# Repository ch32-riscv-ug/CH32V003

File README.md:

# CH32V003

<!-- This file is generated from ch32-riscv-ug/ch32-device-data (index/ + evidence/ + pipeline/build/build_readme.py). Edit there, not here. -->

[Choose a part](#product-comparison) &middot; [Documents](#documents) &middot; [Pin maps](#pin-maps--alternate-functions) &middot; [Pin viewer](https://ch32-riscv-ug.github.io/ch32-device-data/pins.html?chip=CH32V003) &middot; [Errata](#errata) &middot; [Examples](#evt-examples) &middot; [Address map](#address-map)

## Quick start

Programming and debug: **1-wire SDI** (WCH-Link, `Serial Debug Interface`).

### Debug / serial defaults

Where these land **without writing a remap register**. SWD is live at reset; the UART pads are not -- the pin must still be put into alternate-function mode. See `route` in evidence/README.ja.md.

| Series | SWDIO | SWCLK | UART TX | UART RX |
|---|---|---|---|---|
| CH32V003 | PD1 | - | PD5 (USART1) | PD6 (USART1) |

### Datasheets and reference manual

- CH32V003DS0.PDF (datasheet): [English](https://ch32-riscv-ug.github.io/CH32V003/datasheet_en/CH32V003DS0.PDF) · [中文](https://ch32-riscv-ug.github.io/CH32V003/datasheet_zh/CH32V003DS0.PDF)
- CH32V003RM.PDF (reference manual): [English](https://ch32-riscv-ug.github.io/CH32V003/datasheet_en/CH32V003RM.PDF) · [中文](https://ch32-riscv-ug.github.io/CH32V003/datasheet_zh/CH32V003RM.PDF)

## Series

| Series | Core | ISA | Flash | SRAM | Main clock | VDD | Packages | Products | Official |
|---|---|---|---|---|---|---|---|---|---|
| **CH32V003** | QingKe V2A | RV32EC | 16K | 2K | 48 MHz | 2.7-5.5V | QFN20,SOP16,SOP8,TSSOP20 | 4 | [en](https://www.wch-ic.com/products/CH32V003.html) / [zh](https://www.wch.cn/products/CH32V003.html) |

## Product comparison

### CH32V003 product comparison

Only the 3 rows that differ between these 4 products; the other 9 are the same for all of them.

| | [CH32V003&#8203;A4M6](https://ch32-riscv-ug.github.io/ch32-device-data/pins.html?chip=CH32V003A4M6)&#8203;(SOP16) | [CH32V003&#8203;F4P6](https://ch32-riscv-ug.github.io/ch32-device-data/pins.html?chip=CH32V003F4P6)&#8203;(TSSOP20) | [CH32V003&#8203;F4U6](https://ch32-riscv-ug.github.io/ch32-device-data/pins.html?chip=CH32V003F4U6)&#8203;(QFN20) | [CH32V003&#8203;J4M6](https://ch32-riscv-ug.github.io/ch32-device-data/pins.html?chip=CH32V003J4M6)&#8203;(SOP8) |
|---|---|---|---|---|
| **GPIO** | 14 | 18 | 18 | 6 |
| ADC Channel No. | 6 | 8 | 8 | 6 |
| SPI | - | 1 | 1 | - |

<details><summary>All 12 rows</summary>

| | [CH32V003&#8203;A4M6](https://ch32-riscv-ug.github.io/ch32-device-data/pins.html?chip=CH32V003A4M6)&#8203;(SOP16) | [CH32V003&#8203;F4P6](https://ch32-riscv-ug.github.io/ch32-device-data/pins.html?chip=CH32V003F4P6)&#8203;(TSSOP20) | [CH32V003&#8203;F4U6](https://ch32-riscv-ug.github.io/ch32-device-data/pins.html?chip=CH32V003F4U6)&#8203;(QFN20) | [CH32V003&#8203;J4M6](https://ch32-riscv-ug.github.io/ch32-device-data/pins.html?chip=CH32V003J4M6)&#8203;(SOP8) |
|---|---|---|---|---|
| **Flash** | 16K | 16K | 16K | 16K |
| **SRAM** | 2K | 2K | 2K | 2K |
| **GPIO** | 14 | 18 | 18 | 6 |
| **Temperature** | -40..85C | -40..85C | -40..85C | -40..85C |
| Advanced-control timer | 1 | 1 | 1 | 1 |
| General-purpose timer | 1 | 1 | 1 | 1 |
| Watchdog | 2 | 2 | 2 | 2 |
| System clock source | 3 | 3 | 3 | 3 |
| ADC Channel No. | 6 | 8 | 8 | 6 |
| I2C | 1 | 1 | 1 | 1 |
| SPI | - | 1 | 1 | - |
| USART | 1 | 1 | 1 | 1 |

</details>

## Block diagrams

### CH32V003

System block diagram from the [WCH product page](https://www.wch-ic.com/products/CH32V003.html).

<details><summary>Internal block diagram (datasheet)</summary>

</details>

## Documents

| Document | Kind | English | 中文 |
|---|---|---|---|
| CH32V003DS0.PDF | datasheet | [page](https://www.wch-ic.com/downloads/CH32V003DS0_PDF.html) [mirror](https://ch32-riscv-ug.github.io/CH32V003/datasheet_en/CH32V003DS0.PDF) v1.8 | [page](https://www.wch.cn/downloads/CH32V003DS0_PDF.html) [mirror](https://ch32-riscv-ug.github.io/CH32V003/datasheet_zh/CH32V003DS0.PDF) v1.8 |
| CH32V003RM.PDF | reference-manual | [page](https://www.wch-ic.com/downloads/CH32V003RM_PDF.html) [mirror](https://ch32-riscv-ug.github.io/CH32V003/datasheet_en/CH32V003RM.PDF) v1.9 | [page](https://www.wch.cn/downloads/CH32V003RM_PDF.html) [mirror](https://ch32-riscv-ug.github.io/CH32V003/datasheet_zh/CH32V003RM.PDF) v1.9 |
| CH32V003EVT.ZIP | evt | - | [page](https://www.wch.cn/downloads/CH32V003EVT_ZIP.html) [mirror](https://github.com/ch32-riscv-ug/CH32V003/tree/main/EVT) v2.2 |

### Evaluation boards

- board-manual:en: [CH32V00x Evaluation Board Reference-EN.pdf](https://ch32-riscv-ug.github.io/CH32V003/EVT/PUB/CH32V00x%20Evaluation%20Board%20Reference-EN.pdf)
- board-manual:zh: [CH32V00x评估板说明书.pdf](https://ch32-riscv-ug.github.io/CH32V003/EVT/PUB/CH32V00x%E8%AF%84%E4%BC%B0%E6%9D%BF%E8%AF%B4%E6%98%8E%E4%B9%A6.pdf)
- schematic-pdf: [CH32V00xSCH.pdf](https://ch32-riscv-ug.github.io/CH32V003/EVT/PUB/CH32V00xSCH.pdf)

1 board schematics under `EVT/PUB/SCHPCB/`: `CH32V003F4P6-R0`

## Packages & pinout drawings

Pinout drawings are in the datasheet (chapter *Pinouts*); each link opens at the page that carries the drawing:

| Package | Products | Datasheet | Outline |
|---|---|---|---|
| SOP16 | CH32V003A4M6 | [en](https://ch32-riscv-ug.github.io/CH32V003/datasheet_en/CH32V003DS0.PDF#page=12) / [zh](https://ch32-riscv-ug.github.io/CH32V003/datasheet_zh/CH32V003DS0.PDF#page=9) | [drawing](https://raw.githubusercontent.com/ch32-riscv-ug/WCH-common/main/image/package_SOP16.png) |
| TSSOP20 | CH32V003F4P6 | [en](https://ch32-riscv-ug.github.io/CH32V003/datasheet_en/CH32V003DS0.PDF#page=12) / [zh](https://ch32-riscv-ug.github.io/CH32V003/datasheet_zh/CH32V003DS0.PDF#page=9) | [drawing](https://raw.githubusercontent.com/ch32-riscv-ug/WCH-common/main/image/package_TSSOP20.png) |
| QFN20 | CH32V003F4U6 | [en](https://ch32-riscv-ug.github.io/CH32V003/datasheet_en/CH32V003DS0.PDF#page=12) / [zh](https://ch32-riscv-ug.github.io/CH32V003/datasheet_zh/CH32V003DS0.PDF#page=9) | [drawing](https://raw.githubusercontent.com/ch32-riscv-ug/WCH-common/main/image/package_QFN20.png) |
| SOP8 | CH32V003J4M6 | [en](https://ch32-riscv-ug.github.io/CH32V003/datasheet_en/CH32V003DS0.PDF#page=13) / [zh](https://ch32-riscv-ug.github.io/CH32V003/datasheet_zh/CH32V003DS0.PDF#page=9) | [drawing](https://raw.githubusercontent.com/ch32-riscv-ug/WCH-common/main/image/package_SOP8.png) |

## Pin maps & alternate functions

> [!NOTE]
> These are the **pin-table superset**: the datasheet prints one pad table for every product that shares a pinout, so a pad row does not mean this part has the peripheral. Use the product comparison table above for what a given part number contains.

### CH32V003 pin map

Pin functions (filterable): [ALL](https://ch32-riscv-ug.github.io/ch32-device-data/pins.html?chip=CH32V003) [ADC](https://ch32-riscv-ug.github.io/ch32-device-data/pins.html?chip=CH32V003&features=ADC) [I2C](https://ch32-riscv-ug.github.io/ch32-device-data/pins.html?chip=CH32V003&features=I2C) [SPI](https://ch32-riscv-ug.github.io/ch32-device-data/pins.html?chip=CH32V003&features=SPI) [SYS](https://ch32-riscv-ug.github.io/ch32-device-data/pins.html?chip=CH32V003&features=SYS) [TIM](https://ch32-riscv-ug.github.io/ch32-device-data/pins.html?chip=CH32V003&features=TIM) [UART](https://ch32-riscv-ug.github.io/ch32-device-data/pins.html?chip=CH32V003&features=UART) [USB](https://ch32-riscv-ug.github.io/ch32-device-data/pins.html?chip=CH32V003&features=USB)

| Pin name | Type | [CH32V003&#8203;A4M6](https://ch32-riscv-ug.github.io/ch32-device-data/pins.html?chip=CH32V003A4M6)&#8203;(SOP16) | [CH32V003&#8203;F4P6](https://ch32-riscv-ug.github.io/ch32-device-data/pins.html?chip=CH32V003F4P6)&#8203;(TSSOP20) | [CH32V003&#8203;F4U6](https://ch32-riscv-ug.github.io/ch32-device-data/pins.html?chip=CH32V003F4U6)&#8203;(QFN20) | [CH32V003&#8203;J4M6](https://ch32-riscv-ug.github.io/ch32-device-data/pins.html?chip=CH32V003J4M6)&#8203;(SOP8) | Notes |
|---|---|---|---|---|---|---|
| PA1 | I/O/A | 12 | 5 | 2 | 1 | OSC |
| PA2 | I/O/A | 13 | 6 | 3 | 3 | OSC |
| PC0 | I/O | 16 | 10 | 7 | - |  |
| PC1 | I/O/FT | 1 | 11 | 8 | 5 |  |
| PC2 | I/O/FT | 2 | 12 | 9 | 6 |  |
| PC3 | I/O | 3 | 13 | 10 | - |  |
| PC4 | I/O/A | 4 | 14 | 11 | 7 |  |
| PC5 | I/O/FT | - | 15 | 12 | - |  |
| PC6 | I/O/FT | 5 | 16 | 13 | - |  |
| PC7 | I/O | 6 | 17 | 14 | - |  |
| PD0 | I/O/A | - | 8 | 5 | - |  |
| PD1 | I/O/A | 7 | 18 | 15 | 8 | SWDIO |
| PD2 | I/O/A | - | 19 | 16 | - |  |
| PD3 | I/O/A | - | 20 | 17 | - |  |
| PD4 | I/O/A | 8 | 1 | 18 | 8 |  |
| PD5 | I/O/A | 9 | 2 | 19 | 8 | UART TX (USART1) |
| PD6 | I/O/A | 10 | 3 | 20 | 1 | UART RX (USART1) |
| PD7 | I/O/A | 11 | 4 | 1 | - |  |
| VDD | P | 15 | 9 | 6 | 4 |  |
| VSS | P | 14 | 7 | 4/EP | 2 |  |

<details><summary><b>CH32V003 alternate functions</b></summary>

| Pad | default | (no route stated) | remap-1 | remap-2 | remap-3 |
|---|---|---|---|---|---|
| PA1 | A1, OPN0, T1CH2 | OSCI | - | T1CH2 | - |
| PA2 | A0, OPP0, T1CH2N | OSCO | AETR2 | T1CH2N | - |
| PC0 | T2CH3 | - | NSS, T1CH3 | T2CH3 | UTX |
| PC1 | NSS, SDA | - | T1BKIN, T2CH4 | T2CH1ETR | T1BKIN, T2CH1ETR, URX |
| PC2 | SCL, T1BKIN, URTS | - | AETR, T2CH2, URTS | T1BKIN | T1ETR |
| PC3 | T1CH3 | - | T1CH1N, UCTS | T1CH3 | T1CH1N |
| PC4 | A2, MCO, T1CH4 | - | T1CH2N | T1CH4 | T1CH1 |
| PC5 | SCK, T1ETR | - | SCK, T1ETR, T2CH1ETR | SCL | SCL, T1CH3, UCK |
| PC6 | MOSI | - | MOSI, T1CH1 | SDA, UCTS | SDA, T1CH3N, UCTS |
| PC7 | MISO | - | MISO, T1CH2 | URTS | T1CH2, T2CH2, URTS |
| PD0 | OPN1, T1CH1N | - | SDA, UTX | T1CH1N | - |
| PD1 | AETR2, SWIO, T1CH3N | - | SCL, T1CH3N, URX | T1CH3N | - |
| PD2 | A3, T1CH1 | - | T2CH3 | T1CH1 | T1CH2N |
| PD3 | A4, AETR, T2CH2, UCTS | - | T1CH4 | T2CH2 | - |
| PD4 | A7, OPO, T2CH1ETR, UCK | - | - | TIETR | T1CH4 |
| PD5 | A5, UTX | - | - | URX | T2CH4 |
| PD6 | A6, URX | - | - | UTX | T2CH3 |
| PD7 | NRST, OPP1, T2CH4 | - | UCK | T2CH4, UCK | - |

</details>

<details><summary><b>Remap selectors (AFIO)</b></summary>

| Series | Field | Register | Bits | Values | Reset |
|---|---|---|---|---|---|
| CH32V003 | ADC1_ETRGINJ_REMAP | PCFR1 | PCFR1:17 | 0;1 | 0 |
| CH32V003 | ADC1_ETRGREG_REMAP | PCFR1 | PCFR1:18 | 0;1 | 0 |
| CH32V003 | I2C1_REMAP | PCFR1 | PCFR1:1;PCFR1:22 | 0;1;2;3 | 0 |
| CH32V003 | SPI1_REMAP | PCFR1 | PCFR1:0 | 0;1 | 0 |
| CH32V003 | TIM1_REMAP | PCFR1 | PCFR1:6;PCFR1:7 | 0;1;2;3 | 0 |
| CH32V003 | TIM2_REMAP | PCFR1 | PCFR1:8;PCFR1:9 | 0;1;2;3 | 0 |
| CH32V003 | USART1_REMAP | PCFR1 | PCFR1:2;PCFR1:21 | 0;1;2;3 | 0 |

</details>

## Errata

- Only UNIID1 and UNIID2 (the low 64 bits) of the unique ID differ between chips; UNIID3 is not unique although the reference manual describes a 96-bit unique identifier. UNIID3 reads 0xFFFFFFFF on the measured V003, V006, X035 and L103 chips, and the same 0xE339E339 on a V203 and a V307. Use UNIID1|UNIID2 as the chip's unique value. *(applies: CH32L103, CH32V003, CH32V006, CH32V203, CH32V307, CH32X035; )*

## EVT examples

62 routines in [EVT/EXAM](https://github.com/ch32-riscv-ug/CH32V003/tree/main/EVT/EXAM):

[ADC](https://github.com/ch32-riscv-ug/CH32V003/tree/main/EVT/EXAM/ADC) 6 · [APPLICATION](https://github.com/ch32-riscv-ug/CH32V003/tree/main/EVT/EXAM/APPLICATION) 1 · [DMA](https://github.com/ch32-riscv-ug/CH32V003/tree/main/EVT/EXAM/DMA) 2 · [EXTI](https://github.com/ch32-riscv-ug/CH32V003/tree/main/EVT/EXAM/EXTI) 1 · [FLASH](https://github.com/ch32-riscv-ug/CH32V003/tree/main/EVT/EXAM/FLASH) 2 · [GPIO](https://github.com/ch32-riscv-ug/CH32V003/tree/main/EVT/EXAM/GPIO) 1 · [I2C](https://github.com/ch32-riscv-ug/CH32V003/tree/main/EVT/EXAM/I2C) 6 · [IAP](https://github.com/ch32-riscv-ug/CH32V003/tree/main/EVT/EXAM/IAP) 1 · [INT](https://github.com/ch32-riscv-ug/CH32V003/tree/main/EVT/EXAM/INT) 2 · [IWDG](https://github.com/ch32-riscv-ug/CH32V003/tree/main/EVT/EXAM/IWDG) 1 · [OPA](https://github.com/ch32-riscv-ug/CH32V003/tree/main/EVT/EXAM/OPA) 1 · [PWR](https://github.com/ch32-riscv-ug/CH32V003/tree/main/EVT/EXAM/PWR) 4 · [RCC](https://github.com/ch32-riscv-ug/CH32V003/tree/main/EVT/EXAM/RCC) 2 · [SDI_Printf](https://github.com/ch32-riscv-ug/CH32V003/tree/main/EVT/EXAM/SDI_Printf) 1 · [SPI](https://github.com/ch32-riscv-ug/CH32V003/tree/main/EVT/EXAM/SPI) 5 · [SYSTICK](https://github.com/ch32-riscv-ug/CH32V003/tree/main/EVT/EXAM/SYSTICK) 1 · [TIM](https://github.com/ch32-riscv-ug/CH32V003/tree/main/EVT/EXAM/TIM) 16 · [USART](https://github.com/ch32-riscv-ug/CH32V003/tree/main/EVT/EXAM/USART) 8 · [WWDG](https://github.com/ch32-riscv-ug/CH32V003/tree/main/EVT/EXAM/WWDG) 1

## Reference

### Address map

| Region | Base | Kind |
|---|---|---|
| APB1PERIPH | `0x40000000` | bus |
| PERIPH | `0x40000000` | bus |
| APB2PERIPH | `0x40010000` | bus |
| AHBPERIPH | `0x40020000` | bus |
| FLASH | `0x00000000` | link-origin |
| RAM | `0x20000000` | link-origin |
| FLASH | `0x08000000` | memory |
| OB | `0x1ffff800` | memory |
| SRAM | `0x20000000` | memory |

`link-origin` is what the EVT linker scripts use; the `memory` row for FLASH is the address the device header states. Both windows are real -- CH32V307 answers at `0x08000000` and at `0x00000000`.

Peripheral base addresses are in [memory_map.csv](https://github.com/ch32-riscv-ug/ch32-device-data/blob/main/index/memory_map.csv); interrupt numbers in [interrupts.csv](https://github.com/ch32-riscv-ug/ch32-device-data/blob/main/index/interrupts.csv).

---
Data: [ch32-device-data](https://github.com/ch32-riscv-ug/ch32-device-data) (evidence/ and index/ -- each value carries its evidence and confidence there).

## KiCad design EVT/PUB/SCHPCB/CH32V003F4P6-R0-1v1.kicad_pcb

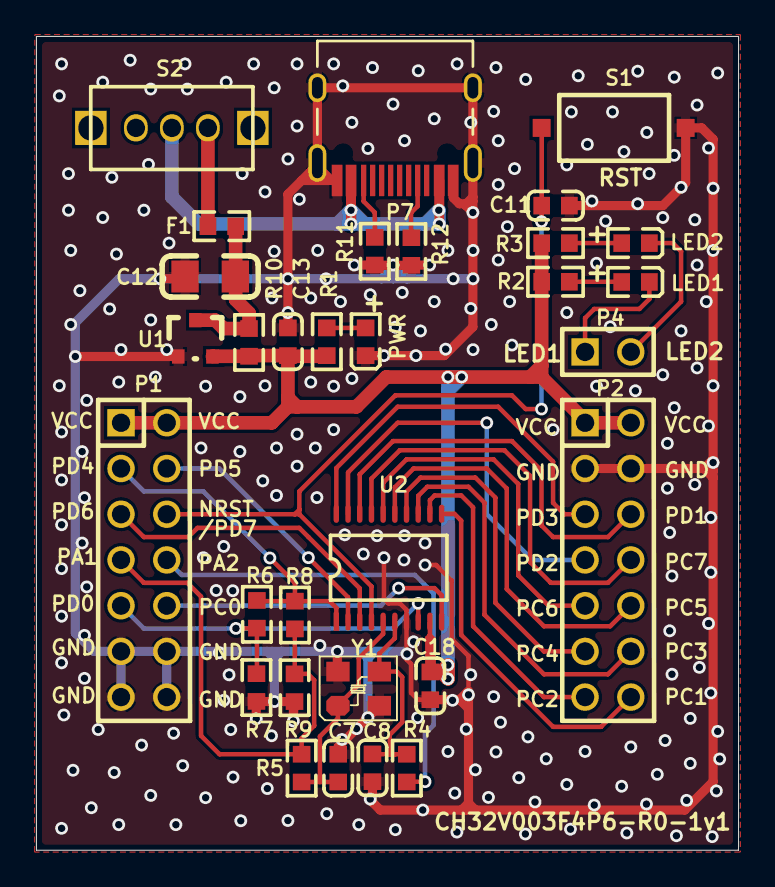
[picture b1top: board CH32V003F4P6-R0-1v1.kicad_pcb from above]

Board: 2 copper layers, 39.0 x 45.2 mm, 31 parts (0 on the bottom side), 32 nets.

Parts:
C7, C8: 22pF; 0603_C
C11, C18: 0.1uF; 0603_C
C12: 10uF; 3216_C
C13: 2.2uF; 0603_C
F1: 500mA; 0603
LED1: LED1 blue; 0603+
LED2: LED2 blue; 0603+
P1, P2: Header 7X2; IDC14-2.54mm
P4: HEADER 2; SIP2-2.54mm
P7: TYPE-C; TYPE-C-Receptacle-2.0
PWR: POWER red; 0603+
R1, R2, R3: 1K; 0603
R4, R5, R6, R7, R8, R9, R10, R11, R12: 0R; 0603
S1: NRST; SMD_6.1x3.65x2.5mm-KEY
S2: SW; SW1
U1: 6219P33M; SOT-23
U2: CH32V003F4P6; TSSOP20
Y1: 24MHz; XT3225

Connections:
+5V: P7.A4, P7.B4, S2.1
GND: C7.1, C8.1, C11.1, C12.2, C13.1, C18.1, P1.11, P1.12, P1.13, P1.14, P2.3, P2.4, P7.0, P7.A1, P7.B1, PWR.2, R7.2, R9.2, R11.2, R12.2, S1.2, U1.1, U2.7, Y1.2, Y1.4
LED1: LED1.2, P4.1
LED2: LED2.2, P4.2
NRST: C11.2, P1.6, S1.1, U2.4
NetC12_1: C12.1, F1.2, R10.1, U1.3
NetF1_1: F1.1, S2.3
NetLED1_1: LED1.1, R2.2
NetLED2_1: LED2.1, R3.2
NetP7_A5: P7.A5, R12.1
NetP7_B5: P7.B5, R11.1
NetPWR_1: PWR.1, R1.1
PA1: P1.7, R5.2, R8.2, R9.1
PA2: P1.8, R4.2
PC0: P1.10, U2.10
PC1: P2.14, U2.11
PC2: P2.13, U2.12
PC3: P2.12, U2.13
PC4: P2.11, U2.14
PC5: P2.10, U2.15
PC6: P2.9, U2.16
PC7: P2.8, U2.17
PD0: P1.9, R6.2, R7.1, U2.8
PD1: P2.6, U2.18
PD2: P2.7, U2.19
PD3: P2.5, U2.20
PD4: P1.3, R6.1, R8.1, U2.1
PD5: P1.4, U2.2
PD6: P1.5, U2.3
VCC: C13.2, C18.2, P1.1, P1.2, P2.1, P2.2, R1.2, R2.1, R3.1, R10.2, U1.2, U2.9
XI: C7.2, R5.1, U2.5, Y1.1
XO: C8.2, R4.1, U2.6, Y1.3

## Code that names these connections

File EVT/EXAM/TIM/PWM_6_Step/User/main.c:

/********************************** (C) COPYRIGHT *******************************
 * File Name          : main.c
 * Author             : WCH
 * Version            : V1.0.0
 * Date               : 2024/11/25
 * Description        : Main program body.
*********************************************************************************
* Copyright (c) 2021 Nanjing Qinheng Microelectronics Co., Ltd.
* Attention: This software (modified or not) and binary are used for 
* microcontroller manufactured by Nanjing Qinheng Microelectronics.
*******************************************************************************/

/*
 *@Note
 * 6_six_PWM output routine:
 * TIM1_CH1(PC4) TIM1_CH1N(PC3)
 * TIM1_CH2(PC7) TIM1_CH2N(PD2)
 * TIM1_CH3(PC5) TIM1_CH3N(PC6)
 * Only advanced timer (channel 1,2,3) have this function.
*/

#include "debug.h"

/*********************************************************************
 * @fn      TIM1_PWMOut_Init
 *
 * @brief   Initializes TIM1 output compare.
 *
 * @param   arr - the period value.
 *          psc - the prescaler value.
 *          ccp - the pulse value.
 *
 * @return  none
 */
void TIM1_PWMOut_Init( u16 arr, u16 psc, u16 ccp )
{
    GPIO_InitTypeDef GPIO_InitStructure={0};
    TIM_OCInitTypeDef TIM_OCInitStructure={0};
    TIM_TimeBaseInitTypeDef TIM_TimeBaseInitStructure={0};

    RCC_APB2PeriphClockCmd( RCC_APB2Periph_AFIO |RCC_APB2Periph_GPIOC |RCC_APB2Periph_GPIOD | RCC_APB2Periph_TIM1, ENABLE );
    GPIO_PinRemapConfig(GPIO_FullRemap_TIM1, ENABLE);

    GPIO_InitStructure.GPIO_Pin = GPIO_Pin_3|GPIO_Pin_4|GPIO_Pin_5|GPIO_Pin_6|GPIO_Pin_7;
    GPIO_InitStructure.GPIO_Mode = GPIO_Mode_AF_PP;
    GPIO_InitStructure.GPIO_Speed = GPIO_Speed_30MHz;
    GPIO_Init( GPIOC, &GPIO_InitStructure );
    GPIO_InitStructure.GPIO_Pin = GPIO_Pin_2;
    GPIO_Init( GPIOD, &GPIO_InitStructure );

    TIM_TimeBaseInitStructure.TIM_Period = arr;
    TIM_TimeBaseInitStructure.TIM_Prescaler = psc;
    TIM_TimeBaseInitStructure.TIM_ClockDivision = TIM_CKD_DIV1;
    TIM_TimeBaseInitStructure.TIM_CounterMode = TIM_CounterMode_Up;
    TIM_TimeBaseInit( TIM1, &TIM_TimeBaseInitStructure);

    TIM_OCInitStructure.TIM_OCMode = TIM_OCMode_PWM1;
    TIM_OCInitStructure.TIM_OutputState = TIM_OutputState_Enable;
    TIM_OCInitStructure.TIM_OutputNState = TIM_OutputNState_Enable;
    TIM_OCInitStructure.TIM_Pulse = ccp;
    TIM_OCInitStructure.TIM_OCPolarity = TIM_OCPolarity_High;
    TIM_OCInitStructure.TIM_OCNPolarity = TIM_OCNPolarity_High;
    TIM_OC1Init( TIM1, &TIM_OCInitStructure );
    TIM_OC2Init( TIM1, &TIM_OCInitStructure );
    TIM_OC3Init( TIM1, &TIM_OCInitStructure );

    TIM_CtrlPWMOutputs(TIM1, ENABLE );
    TIM_OC1PreloadConfig( TIM1, TIM_OCPreload_Disable );
    TIM_OC2PreloadConfig( TIM1, TIM_OCPreload_Disable );
    TIM_OC3PreloadConfig( TIM1, TIM_OCPreload_Disable );
    TIM_ARRPreloadConfig( TIM1, ENABLE );

    TIM_CCPreloadControl(TIM1, ENABLE);//CCPC
    TIM_SelectCOM(TIM1, ENABLE);//CCUS

    TIM_Cmd( TIM1, ENABLE );
}

/*********************************************************************
 * @fn      main
 *
 * @brief   Main program.
 *
 * @return  none
 */
int main(void)
{

    SystemCoreClockUpdate();
    Delay_Init();
#if (SDI_PRINT == SDI_PR_OPEN)
    SDI_Printf_Enable();
#else
    USART_Printf_Init(115200);
#endif
    printf("SystemClk:%d\r\n",SystemCoreClock);
    printf( "ChipID:%08x\r\n", DBGMCU_GetCHIPID() );
    TIM1_PWMOut_Init( 100-1, 48000-1, 75 );

    TIM_CCxCmd(TIM1, TIM_Channel_1, TIM_CCx_Enable);
    TIM_CCxNCmd(TIM1, TIM_Channel_1, TIM_CCxN_Disable);
    TIM_ForcedOC1Config(TIM1, TIM_ForcedAction_Active);

    TIM_CCxCmd(TIM1, TIM_Channel_2, TIM_CCx_Disable);
    TIM_CCxNCmd(TIM1, TIM_Channel_2, TIM_CCxN_Enable);
    TIM_ForcedOC2Config(TIM1, TIM_ForcedAction_InActive);

    TIM_CCxCmd(TIM1, TIM_Channel_3, TIM_CCx_Enable);
    TIM_CCxNCmd(TIM1, TIM_Channel_3, TIM_CCxN_Enable);
    TIM_ForcedOC3Config(TIM1, TIM_ForcedAction_InActive);

    Delay_Ms(500);

    TIM_GenerateEvent(TIM1, TIM_EventSource_COM);

    while(1);
}

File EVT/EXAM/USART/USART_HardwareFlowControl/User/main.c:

/********************************** (C) COPYRIGHT *******************************
 * File Name          : main.c
 * Author             : WCH
 * Version            : V1.0.1
 * Date               : 2026/10/16
 * Description        : Main program body.
 *********************************************************************************
 * Copyright (c) 2021 Nanjing Qinheng Microelectronics Co., Ltd.
 * Attention: This software (modified or not) and binary are used for 
 * microcontroller manufactured by Nanjing Qinheng Microelectronics.
 *******************************************************************************/

/*
 *@Note
 Hardware flow control mode, master/slave mode, transceiver routine:
 USART1_Tx(PD5)\USART1_Rx(PD6)\USART1_CTS(PD3)\USART1_RTS(PC2)
 This example demonstrates UART1 hardware flow control data sending and receiving,
 connect the UART1 Tx and Rx pins to the serial port tool respectively,View through
 the host computer tool, CTS is connected to VCC, and data cannot be sent, but
 connected to GND, data can be sent normally.

*/

#include "debug.h"

/* Global typedef */
typedef enum
{
    FAILED = 0,
    PASSED = !FAILED
} TestStatus;

/* Global define */
#define TxSize     (size(TxBuffer))
#define size(a)    (sizeof(a) / sizeof(*(a)))

/* Global Variable */
u8 TxBuffer[] = "USART1 Hardware Flow Control Example: USART1-\
Hyperterminal communication using hardware flow control\n\r";
u8 RxBuffer[TxSize] = {0};
u8 TxCnt = 0, RxCnt = 0;

/*********************************************************************
 * @fn      Buffercmp
 *
 * @brief   Compares two buffers
 *
 * @param   Buf1,Buf2 - buffers to be compared
 *          BufferLength - buffer's length
 *
 * @return  PASSED - Buf1 identical to Buf
 *          FAILED - Buf1 differs from Buf2
 */
TestStatus Buffercmp(uint8_t *Buf1, uint8_t *Buf2, uint16_t BufLength)
{
    while(BufLength--)
    {
        if(*Buf1 != *Buf2)
        {
            return FAILED;
        }
        Buf1++;
        Buf2++;
    }
    return PASSED;
}

/*********************************************************************
 * @fn      USART1_ReCFG
 *
 * @brief   Reinitialize the USART1.
 *
 * @return  none
 */
void USART1_ReCFG(void)
{
    GPIO_InitTypeDef  GPIO_InitStructure = {0};
    USART_InitTypeDef USART_InitStructure = {0};

    RCC_APB2PeriphClockCmd(RCC_APB2Periph_GPIOD | RCC_APB2Periph_GPIOC | RCC_APB2Periph_USART1, ENABLE);

    /* USART1 TX-->D.5   RX-->D.6 */
    GPIO_InitStructure.GPIO_Pin = GPIO_Pin_5;
    GPIO_InitStructure.GPIO_Speed = GPIO_Speed_30MHz;
    GPIO_InitStructure.GPIO_Mode = GPIO_Mode_AF_PP;
    GPIO_Init(GPIOD, &GPIO_InitStructure);
    GPIO_InitStructure.GPIO_Pin = GPIO_Pin_2; /* RTS-->C.2 */
    GPIO_Init(GPIOC, &GPIO_InitStructure);

    GPIO_InitStructure.GPIO_Pin = GPIO_Pin_6;
    GPIO_InitStructure.GPIO_Mode = GPIO_Mode_IN_FLOATING;
    GPIO_Init(GPIOD, &GPIO_InitStructure);
    GPIO_InitStructure.GPIO_Pin = GPIO_Pin_3; /* CTS-->D.3 */
    GPIO_Init(GPIOD, &GPIO_InitStructure);

    USART_InitStructure.USART_BaudRate = 115200;
    USART_InitStructure.USART_WordLength = USART_WordLength_8b;
    USART_InitStructure.USART_StopBits = USART_StopBits_1;
    USART_InitStructure.USART_Parity = USART_Parity_No;
    USART_InitStructure.USART_HardwareFlowControl = USART_HardwareFlowControl_RTS_CTS;
    USART_InitStructure.USART_Mode = USART_Mode_Tx | USART_Mode_Rx;

    USART_Init(USART1, &USART_InitStructure);
    USART_Cmd(USART1, ENABLE);
}

/*********************************************************************
 * @fn      main
 *
 * @brief   Main program.
 *
 * @return  none
 */
int main(void)
{
    NVIC_PriorityGroupConfig(NVIC_PriorityGroup_1);
    SystemCoreClockUpdate();
    Delay_Init();
    USART1_ReCFG();

    printf("USART1 Hardware Flow Control TEST\r\n");
    printf( "ChipID:%08x\r\n", DBGMCU_GetCHIPID() );
    while(TxCnt < TxSize)
    {
        USART_SendData(USART1, TxBuffer[TxCnt++]);
        while(USART_GetFlagStatus(USART1, USART_FLAG_TXE) == RESET);
    }
    do
    {
        if((USART_GetFlagStatus(USART1, USART_FLAG_RXNE) != RESET) && (RxCnt < TxSize))
        {
            RxBuffer[RxCnt] = USART_ReceiveData(USART1);
            USART_SendData(USART1, RxBuffer[RxCnt++]); /* send it when receive a byte */
        }
    } while((RxCnt == 0) || ((RxBuffer[RxCnt - 1] != '\r') && (RxCnt != TxSize)));

    while(1)
    {
    }
}

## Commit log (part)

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2024-05-15 Rename architecture.png to architecture_CH32V003.png
2024-05-15 Rename system.png to system_CH32V003.png
2026-06-15 update update.sh and add GitHub Actions workflow for automated datasheet downloads
2026-06-15 update cron schedule in GitHub Actions workflow and enhance download script with retry logic
2026-06-15 refactor update job to simplify commit logic in GitHub Actions workflow
2026-06-16 update GitHub Actions schedule
2026-06-19 update GitHub Actions workflow to implement keepalive logic and remove unnecessary permissions
2026-06-19 refactor fetch function in update.sh to simplify error handling and remove retry logic
